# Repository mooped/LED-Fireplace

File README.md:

Joiners for ws2812 Fireplace
============================

PCBs to ease wiring of large matrices of ws2812 based LED strips.

Chainable for strips wired in a zigzag fashion from left to right (as seen from the front).

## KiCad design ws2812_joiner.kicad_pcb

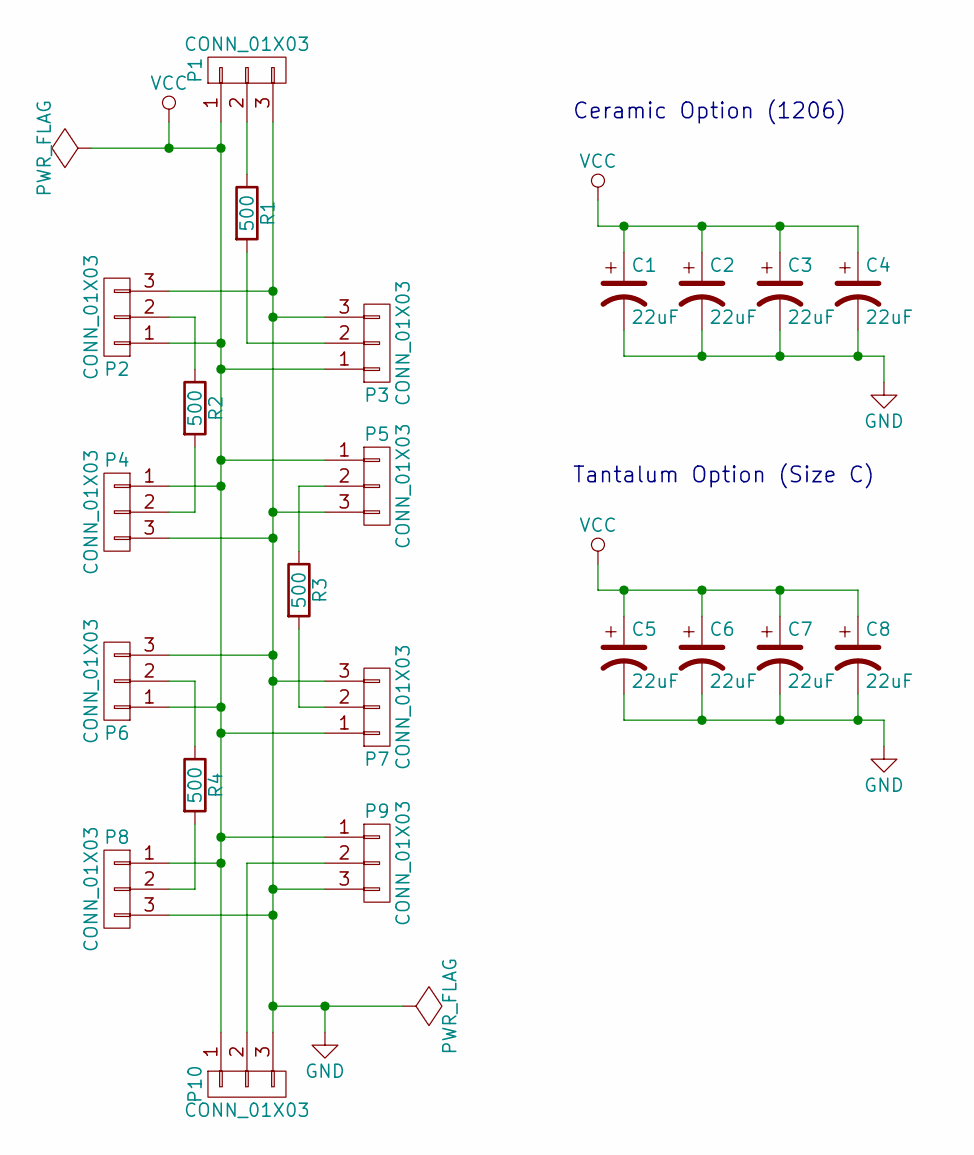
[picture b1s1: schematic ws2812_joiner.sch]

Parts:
C1, C2, C3, C4: 22uF; CP_Tantalum_Case-C_EIA-6032-28_Reflow
C5, C6, C7, C8: 22uF; C_1206_HandSoldering
P1: CONN_01X03; Pin_Header_Angled_1x03_Pitch2.54mm
P2, P3, P4, P5, P6, P7, P8, P9: CONN_01X03; Pad_Array_1x3
P10: CONN_01X03; Socket_Strip_Angled_1x03_Pitch2.54mm
R1, R2, R3, R4: 500; R_1206_HandSoldering

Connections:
GND: C1.2, C2.2, C3.2, C4.2, C5.2, C6.2, C7.2, C8.2, P1.3, P2.3, P3.3, P4.3, P5.3, P6.3, P7.3, P8.3, P9.3, P10.3
unnamed: P1.2, R1.1
unnamed: P2.2, R2.1
unnamed: P3.2, R1.2
unnamed: P4.2, R2.2
unnamed: P5.2, R3.1
unnamed: P6.2, R4.1
unnamed: P7.2, R3.2
unnamed: P8.2, R4.2
unnamed: P9.2, P10.2
VCC: C1.1, C2.1, C3.1, C4.1, C5.1, C6.1, C7.1, C8.1, P1.1, P2.1, P3.1, P4.1, P5.1, P6.1, P7.1, P8.1, P9.1, P10.1

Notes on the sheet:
Ceramic Option (1206)
Tantalum Option (Size C)

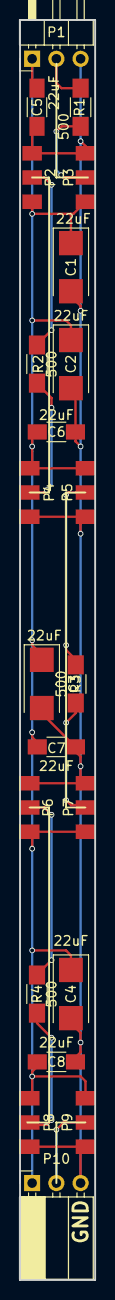
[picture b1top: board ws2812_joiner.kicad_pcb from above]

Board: 2 copper layers, 7.9 x 132.1 mm, 22 parts (0 on the bottom side), 11 nets.

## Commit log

2018-01-07 Initial commit - v0.1 of the board. Messy but with space for large through hole caps.
2018-01-07 Version 2 - use SMD tantalum caps to neaten everything up. Duplicate silkscreen graphics to the front where possible and add component values.
2018-01-07 Add readme.
2018-01-07 Add GitHub URL to v0.2.
